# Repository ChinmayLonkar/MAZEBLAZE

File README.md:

# MAZEBLAZE

This repository contains hardware design files for the MAZEBLAZE Bot.This project is in developement and is not ready for final release.

It uses -
* TRCT5000 IR Sensors for following the lines on the maze 
* TB6612FNG Motor Driver for controlling two N20 motors
* ESP32 for control and perform tasks at high speeds and accuracy

Following are some images of the PCB Design

* Top View

* Bottom View

* Front Copper Layer

* Bottom Copper Layer

* Routing

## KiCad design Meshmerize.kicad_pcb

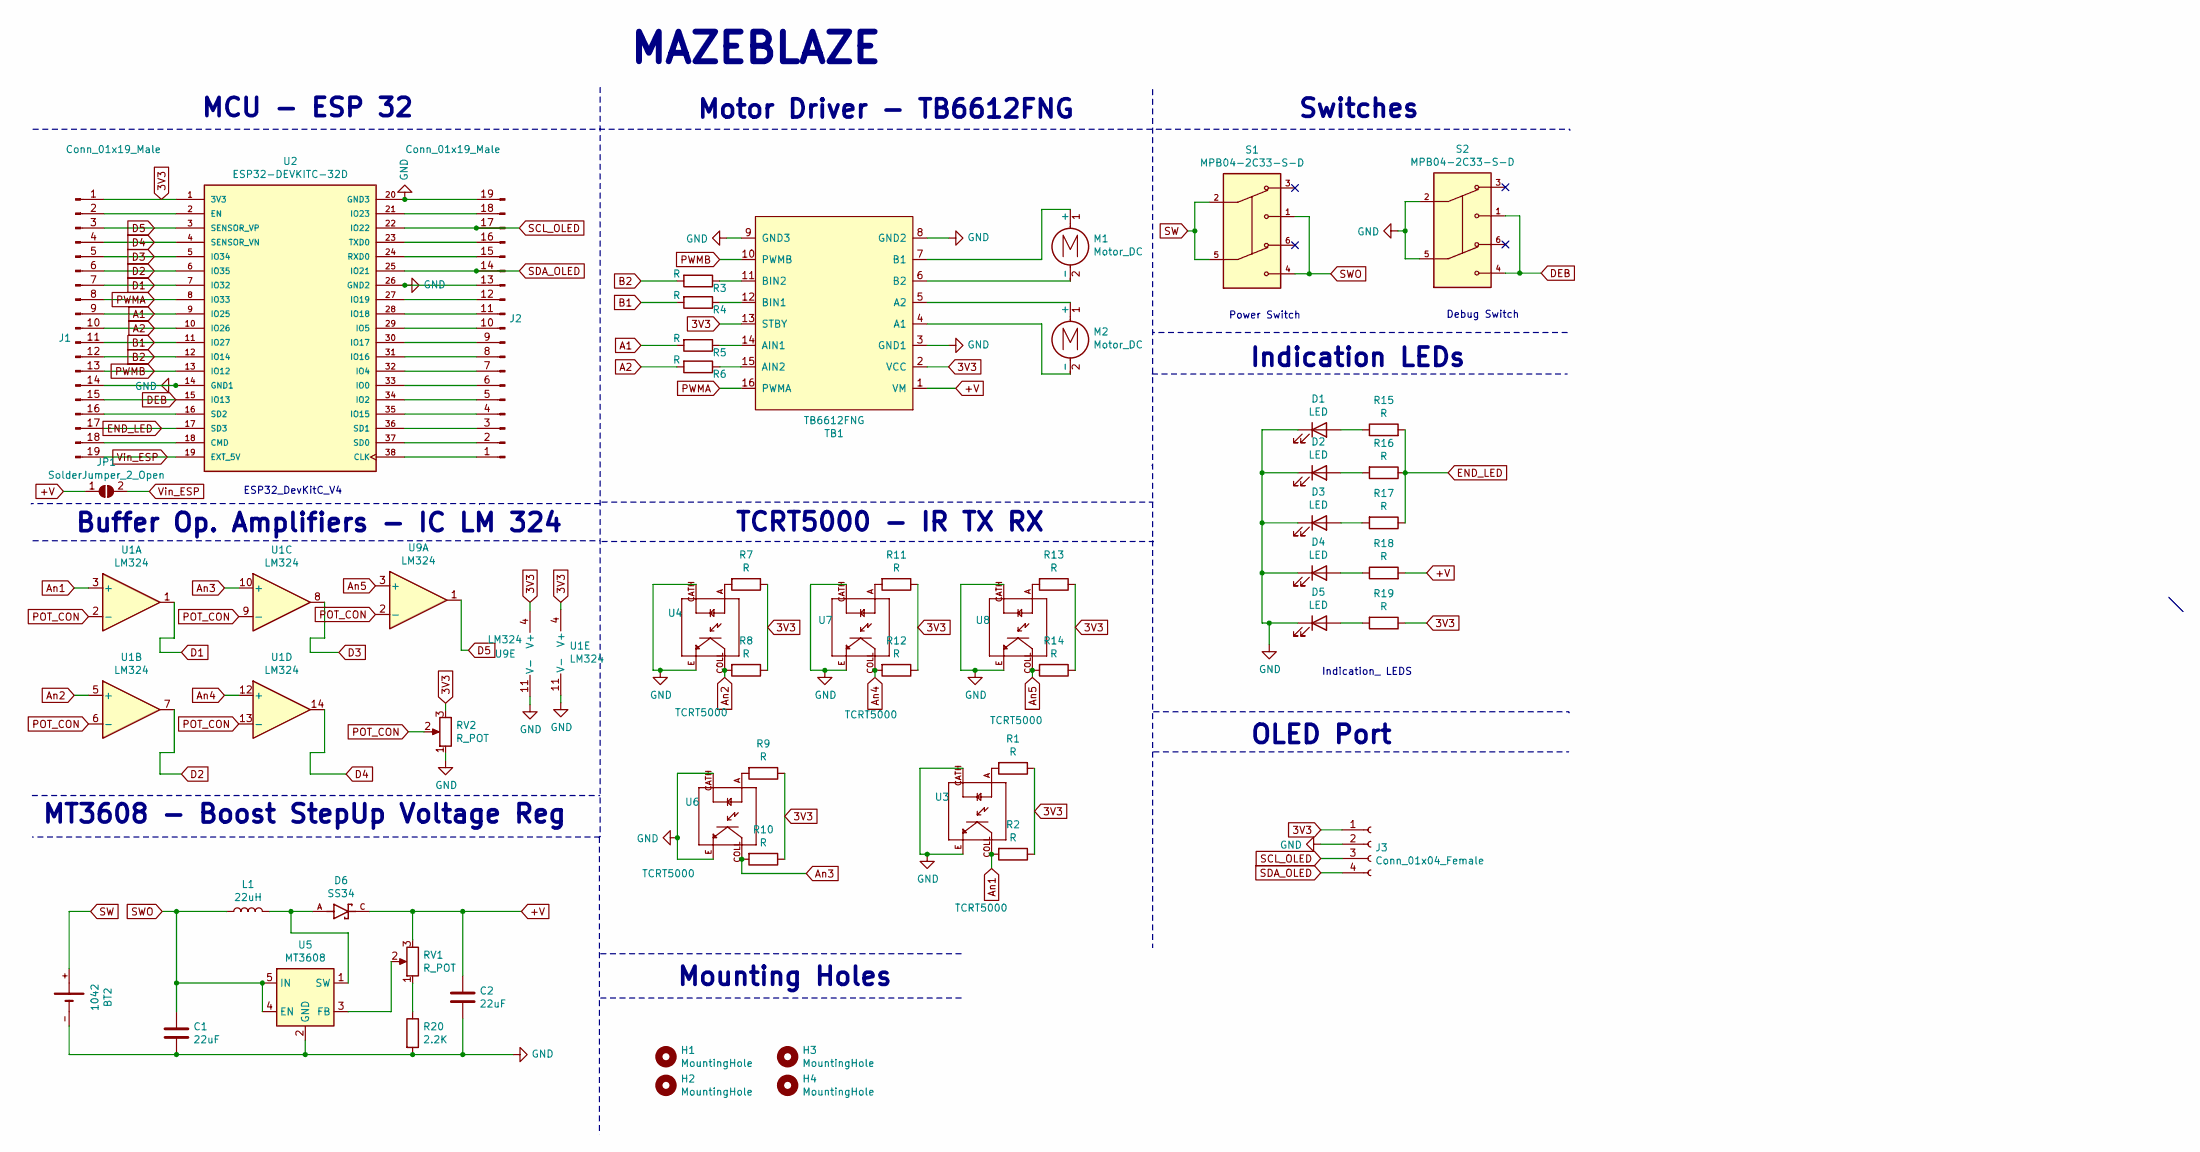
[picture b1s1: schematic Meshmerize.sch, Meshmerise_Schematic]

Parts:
BT2: 1042; BAT_1042
C1, C2: 22uF; C_0805_2012Metric
D1, D2, D3, D4, D5: LED; LED_1206_3216Metric
D6: SS34; DIOM7959X265N; PARTREV 31 Aug 2016
H1, H2, H3, H4: MountingHole; MountingHole_2.2mm_M2
J1, J2: Conn_01x19_Male; PinHeader_1x19_P2.54mm_Vertical
J3: Conn_01x04_Female; PinSocket_1x04_P2.54mm_Vertical
JP1: SolderJumper_2_Open; SolderJumper-2_P1.3mm_Open_Pad1.0x1.5mm
L1: 22uH; L_12x12mm_H6mm
M1, M2: Motor_DC; N20_Motor
R1, R2, R3, R4, R5, R6, R7, R8, R9, R10, R11, R12, R13, R14, R15, R16, R17, R18, R19: R; R_1206_3216Metric
R20: 2.2K; R_1206_3216Metric
RV1, RV2: R_POT; TRIM_3296W-1-202LF
S1, S2: MPB04-2C33-S-D; SW_MPB04-2C33-S-D; PARTREV 1.0
TB1: TB6612FNG
U1, U9: LM324; SOIC-14_3.9x8.7mm_P1.27mm
U2: ESP32-DEVKITC-32D; MODULE_ESP32-DEVKITC-32D; PARTREV 4
U3, U4, U6, U7, U8: TCRT5000; OPTO_TCRT5000; PARTREV 1.7
U5: MT3608; SOT-23-6

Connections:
3V3: J1.1, J3.1, R1.1, R2.1, R7.1, R8.1, R9.1, R10.1, R11.1, R12.1, R13.1, R14.1, R19.1, RV2.3, TB1.2 (VCC), TB1.13 (STBY), U1.4 (V+), U2.1 (3V3), U9.4 (V+)
+V: C2.1, D6.C, JP1.1 (A), R18.2, RV1.3, TB1.1 (VM)
A1: J1.9, R5.2, U2.9 (IO25)
A2: J1.10, R6.2, U2.10 (IO26)
An1: R2.2, U1.3 (+), U3.COLL
An2: R8.2, U1.5 (+), U4.COLL
An3: R10.2, U1.10 (+), U6.COLL
An4: R12.2, U1.12 (+), U7.COLL
An5: R14.2, U8.COLL, U9.3 (+)
B1: J1.11, R4.2, U2.11 (IO27)
B2: J1.12, R3.2, U2.12 (IO14)
D1: J1.7, U1.1, U2.7 (IO32)
D2: J1.6, U1.7, U2.6 (IO35)
D3: J1.5, U1.8, U2.5 (IO34)
D4: J1.4, U1.14, U2.4 (SENSOR_VN)
D5: J1.3, U2.3 (SENSOR_VP), U9.1
DEB: J1.15, S2.1, S2.4, U2.15 (IO13)
END_LED: J1.17, R15.2, R16.1, R17.1, U2.17 (SD3)
GND: BT2.-, C1.2, C2.2, D1.1 (K), D2.1 (K), D3.1 (K), D4.1 (K), D5.1 (K), J1.14, J2.13, J2.19, J3.2, R20.2, RV2.1, S2.2, S2.5, TB1.3 (GND1), TB1.8 (GND2), TB1.9 (GND3), U1.11 (V-), U2.14 (GND1), U2.20 (GND3), U2.26 (GND2), U3.CATH, U3.E, U4.CATH, U4.E, U5.2 (GND), U6.CATH, U6.E, U7.CATH, U7.E, U8.CATH, U8.E, U9.11 (V-)
unnamed: D1.2 (A), R15.1
unnamed: D2.2 (A), R16.2
unnamed: D3.2 (A), R17.2
unnamed: D4.2 (A), R18.1
unnamed: D5.2 (A), R19.2
unnamed: D6.A, L1.2, U5.1 (SW)
unnamed: J1.2, U2.2 (EN)
unnamed: J1.16, U2.16 (SD2)
unnamed: J1.18, U2.18 (CMD)
unnamed: J2.1, U2.38 (CLK)
unnamed: J2.2, U2.37 (SD0)
unnamed: J2.3, U2.36 (SD1)
unnamed: J2.4, U2.35 (IO15)
unnamed: J2.5, U2.34 (IO2)
unnamed: J2.6, U2.33 (IO0)
unnamed: J2.7, U2.32 (IO4)
unnamed: J2.8, U2.31 (IO16)
unnamed: J2.9, U2.30 (IO17)
unnamed: J2.10, U2.29 (IO5)
unnamed: J2.11, U2.28 (IO18)
unnamed: J2.12, U2.27 (IO19)
unnamed: J2.15, U2.24 (RXD0)
unnamed: J2.16, U2.23 (TXD0)
unnamed: J2.18, U2.21 (IO23)
unnamed: M1.1 (+), TB1.7 (B1)
unnamed: M1.2 (-), TB1.6 (B2)
unnamed: M2.1 (+), TB1.5 (A2)
unnamed: M2.2 (-), TB1.4 (A1)
unnamed: R1.2, U3.A
unnamed: R3.1, TB1.11 (BIN2)
unnamed: R4.1, TB1.12 (BIN1)
unnamed: R5.1, TB1.14 (AIN1)
unnamed: R6.1, TB1.15 (AIN2)
unnamed: R7.2, U4.A
unnamed: R9.2, U6.A
unnamed: R11.2, U7.A
unnamed: R13.2, U8.A
unnamed: R20.1, RV1.1
unnamed: RV1.2, U5.3 (FB)
POT_CON: RV2.2, U1.2 (-), U1.6 (-), U1.9 (-), U1.13 (-), U9.2 (-)
PWMA: J1.8, TB1.16 (PWMA), U2.8 (IO33)
PWMB: J1.13, TB1.10 (PWMB), U2.13 (IO12)
SCL_OLED: J2.17, J3.3, U2.22 (IO22)
SDA_OLED: J2.14, J3.4, U2.25 (IO21)
SW: BT2.+, S1.2, S1.5
SWO: C1.1, L1.1, S1.1, S1.4, U5.4 (EN), U5.5 (IN)
Vin_ESP: J1.19, JP1.2 (B), U2.19 (EXT_5V)

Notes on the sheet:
Indication_ LEDS
ESP32_DevKitC_V4
MAZEBLAZE
MCU - ESP 32
Motor Driver - TB6612FNG
Switches
Debug Switch
Power Switch
Buffer Op. Amplifiers - IC LM 324
TCRT5000 - IR TX RX
MT3608 - Boost StepUp Voltage Reg
Mounting Holes
Indication LEDs
OLED Port

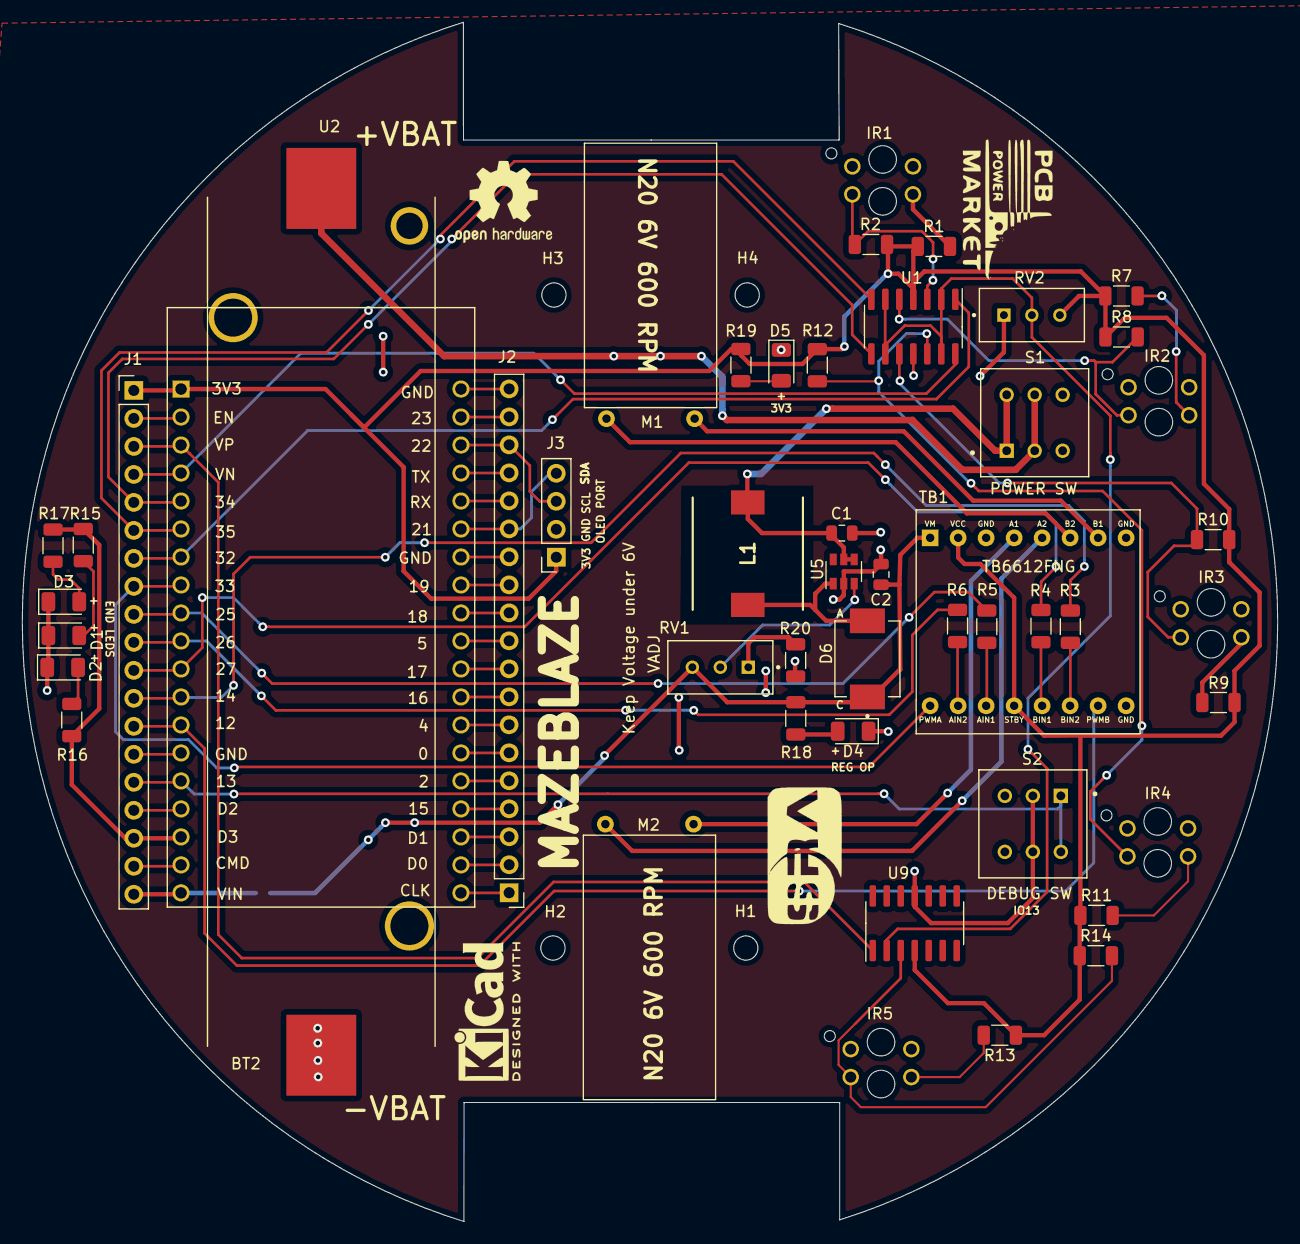
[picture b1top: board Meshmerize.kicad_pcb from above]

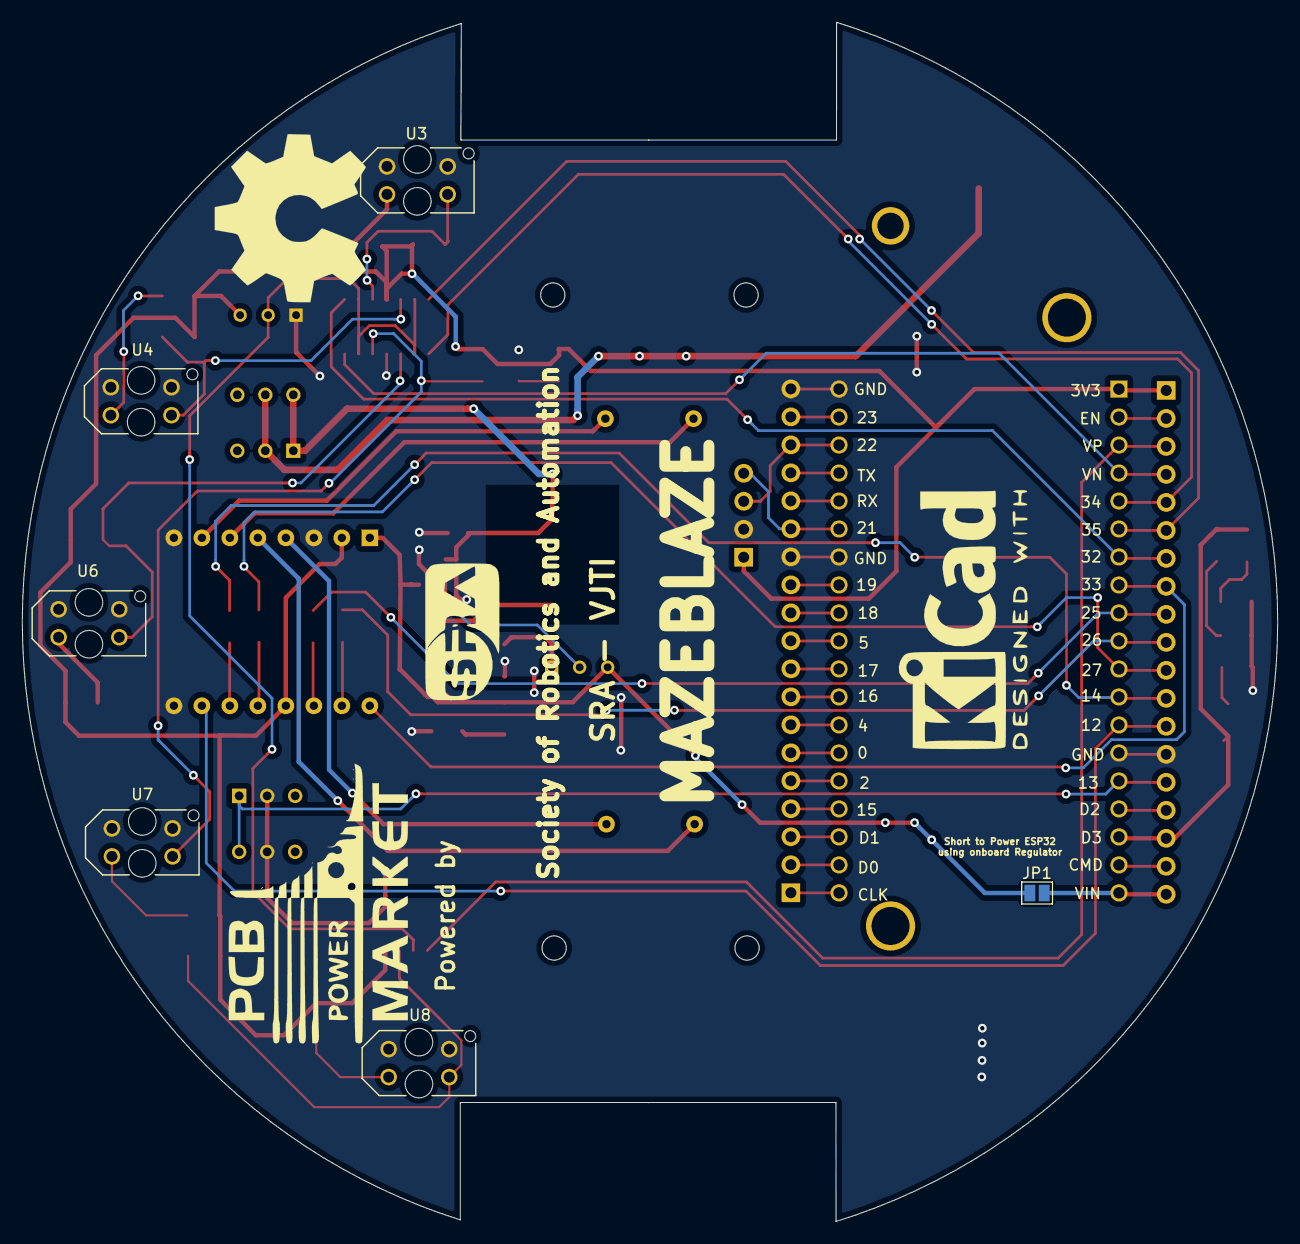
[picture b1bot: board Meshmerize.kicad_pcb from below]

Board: 2 copper layers, 113.9 x 108.8 mm, 54 parts (6 on the bottom side), 66 nets.

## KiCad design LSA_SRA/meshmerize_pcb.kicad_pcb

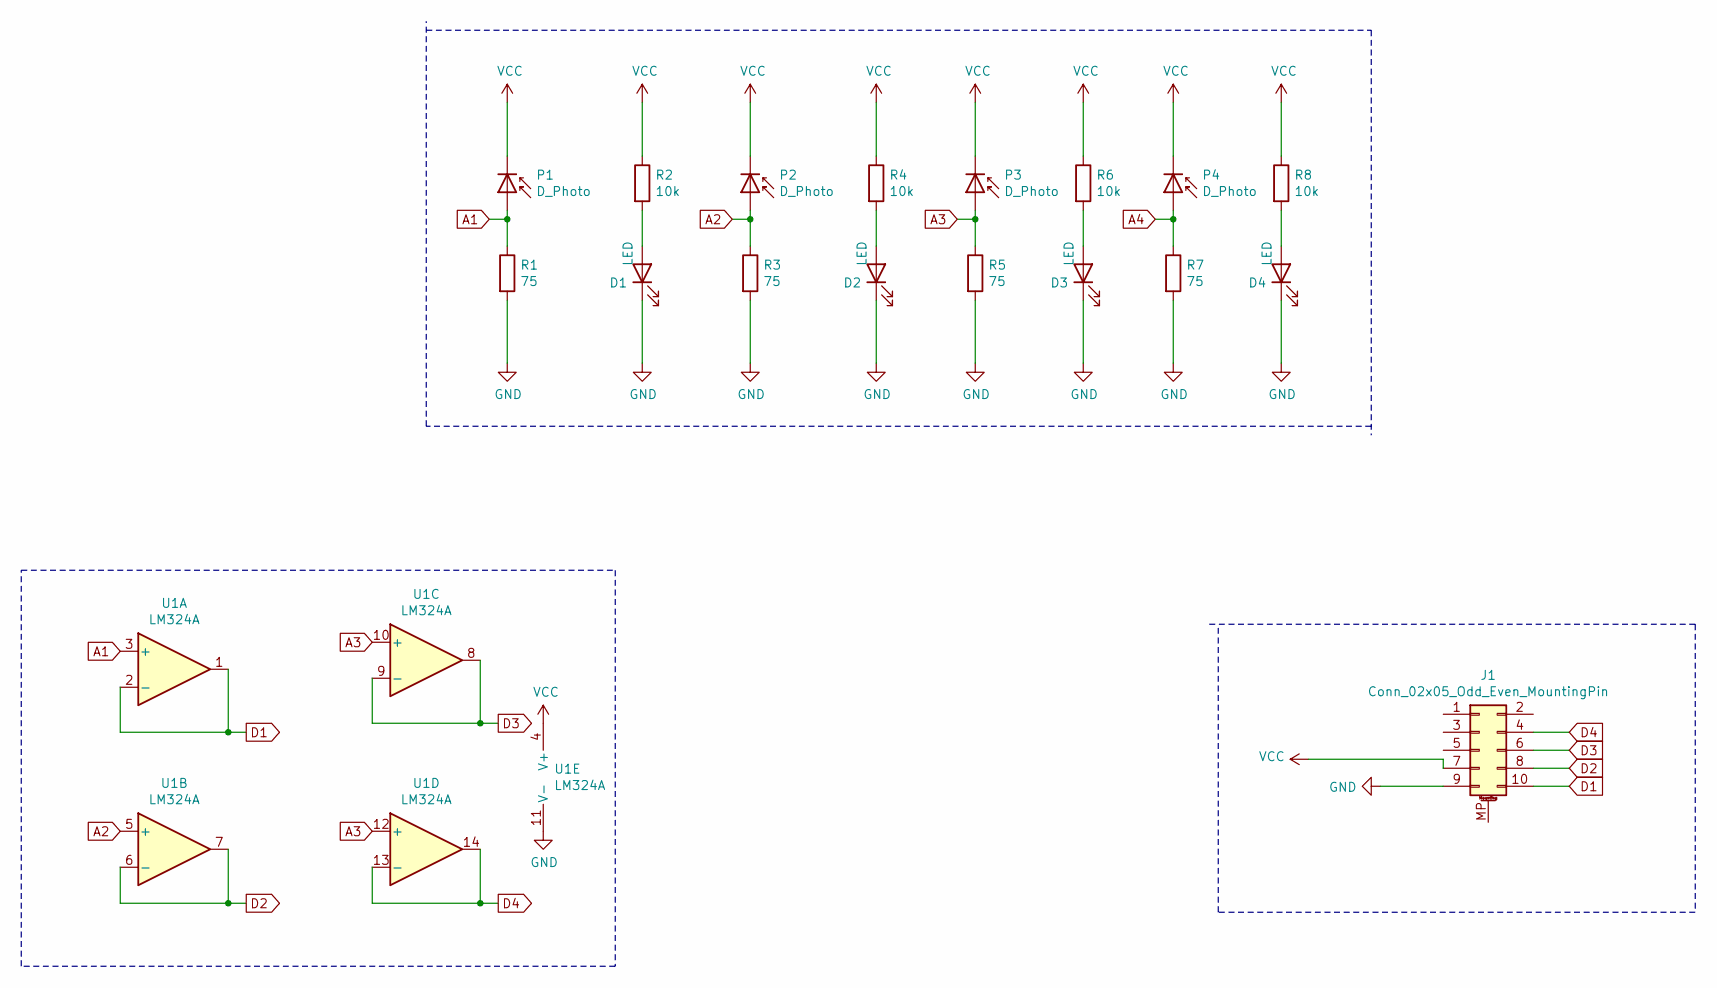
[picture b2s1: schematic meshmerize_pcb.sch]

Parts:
D1, D2, D3, D4: LED; LED_D3.0mm
J1: Conn_02x05_Odd_Even_MountingPin; IDC-Header_2x05-1MP_P2.54mm_Latch6.5mm_Vertical
P1, P2, P3, P4: D_Photo; LED_D5.0mm
R1, R3, R5, R7: 75; R_Axial_DIN0207_L6.3mm_D2.5mm_P10.16mm_Horizontal
R2, R4, R6, R8: 10k; R_Axial_DIN0207_L6.3mm_D2.5mm_P10.16mm_Horizontal
U1: LM324A; LM324-PDIP

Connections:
A1: P1.2 (A), R1.1, U1.3 (+)
A2: P2.2 (A), R3.1, U1.5 (+)
A3: P3.2 (A), R5.1, U1.10 (+), U1.12 (+)
A4: P4.2 (A), R7.1
D1: J1.10, U1.1, U1.2 (-)
D2: J1.8, U1.6 (-), U1.7
D3: J1.6, U1.8, U1.9 (-)
D4: J1.4, U1.13 (-), U1.14
GND: D1.1 (K), D2.1 (K), D3.1 (K), D4.1 (K), J1.9, R1.2, R3.2, R5.2, R7.2, U1.11 (V-)
unnamed: D1.2 (A), R2.2
unnamed: D2.2 (A), R4.2
unnamed: D3.2 (A), R6.2
unnamed: D4.2 (A), R8.2
VCC: J1.7, P1.1 (K), P2.1 (K), P3.1 (K), P4.1 (K), R2.1, R4.1, R6.1, R8.1, U1.4 (V+)

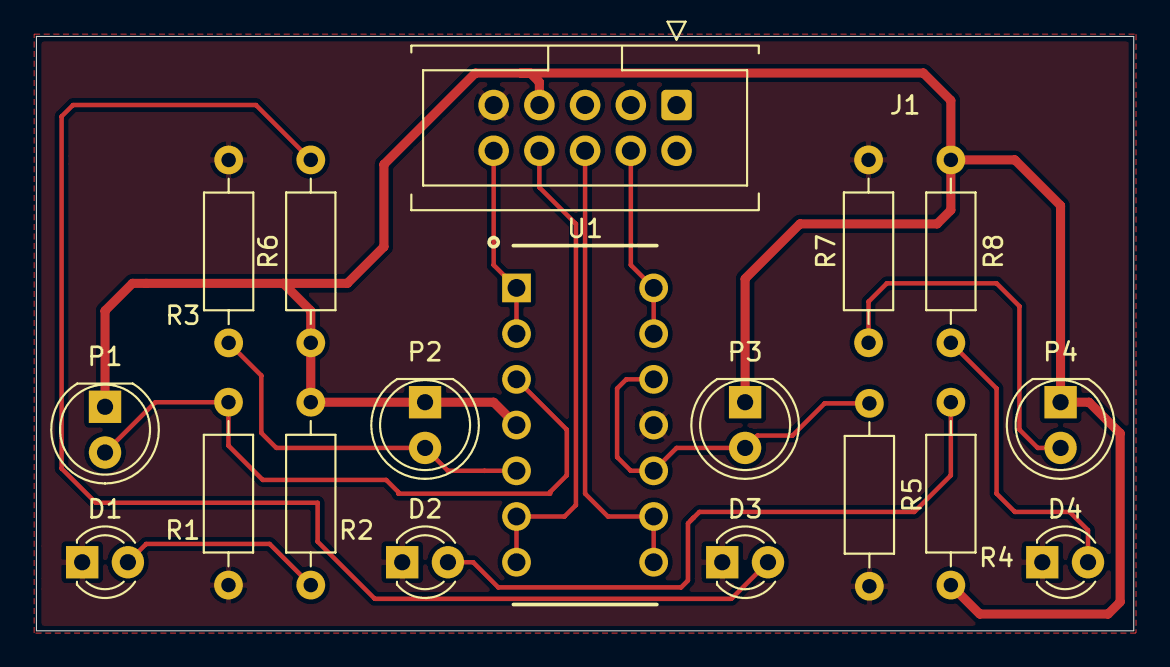
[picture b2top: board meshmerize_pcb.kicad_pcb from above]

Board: 2 copper layers, 61.0 x 33.0 mm, 18 parts (0 on the bottom side), 14 nets.

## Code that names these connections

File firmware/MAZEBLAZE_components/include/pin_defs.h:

#ifndef PIN_DEFS_H
#define PIN_DEFS_H

#define CHECK(x)                \
    do                          \
    {                           \
        esp_err_t __;           \
        if ((__ = x) != ESP_OK) \
            return __;          \
    } while (0)
#define CHECK_LOGE(err, x, tag, msg, ...)      \
    do                                         \
    {                                          \
        if ((err = x) != ESP_OK)               \
        {                                      \
            ESP_LOGE(tag, msg, ##__VA_ARGS__); \
            return err;                        \
        }                                      \
    } while (0)



#define END_LED 10

#define DEBUG_SWITCH 13


#define LSA_D0 32
#define LSA_D1 35
#define LSA_D2 34
#define LSA_D3 39
#define LSA_D4 36

#define SCL_OLED 22
#define SDA_OLED 21

/////// motor driver ////////
//****** normal mode ******//
#define PWM_A 33 //MCPWM_UNIT_1 MCPWM0A
#define AIN_1 25 //MCPWM_UNIT_1 MCPWM0B
#define AIN_2 26 //MCPWM_UNIT_1 MCPWM1A
#define PWM_B 12 //MCPWM_UNIT_1 MCPWM1B
#define BIN_1 27 //MCPWM_UNIT_1 MCPWM2A
#define BIN_2 14 //MCPWM_UNIT_1 MCPWM2B

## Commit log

2021-11-16 Added .gitignore
2021-11-16 Added Kicad project for Meshmerize bot
2021-11-17 Completed PCB Routing
2021-11-17 Changes made in footprint
2021-11-17 Optimized schematics, routing and performed clean up
2021-11-17 Added R-Pot for LSA sensitivity, jumper to power ESP32 using inbuilt regulator, minor optimizations
2021-11-17 Modified Silkscreen and created Gerber Files
2021-11-17 Made minor changes in Back silkscreen and front copper traces
2021-11-17 Stitched Vias for Continuous Ground Plane, minor silkscreen fixes
2021-11-18 Added 3D Files
2021-11-18 Added Logos
2021-11-18 Added silkscreen, asset images, updated renders and gerbers
2021-11-19 Fixed errors, optlized routing
2021-11-19 Updated readme file and gerbers
2021-11-19 Shortened MAZEBLAZE title on B.silk
2021-11-19 Updated Gerbers after minor silkscreen fixes
2021-11-19 Updated Assets with latest render images
2021-11-20 Added firmware
2021-11-23 PCB design files for MAZEBLAZE bot
2021-11-23 Updated firmware with some minor fixes
2021-11-23 Added Motor Component
2021-11-23 Added a basic example for running motor
2021-11-25 Added 4_line_following
2021-11-25 Removed build files
2021-11-26 Added wifi_component
2021-11-26 Implement Wifi for changing PID values
2021-11-27 Setup for White and Black margins
2021-11-27 LSA + Motor control
2021-11-27 made a new function in line_following.c
2021-11-29 Changes made in motor configration as per hardware setup
2021-11-29 Made changes in motor driver component according to hardware setup
2021-11-30 Rearranges file format
2021-11-30 Adds line_following in examples
2021-11-30 Restructures previous code in modular format
2021-12-01 Adds ESP WIFI LOGGER component
2021-12-01 Creates the mazeblaze board component
2021-12-01 Corrects the linefollwing bug
2021-12-01 Adds sdkconfig to gitignore
2021-12-01 Refactores and solves minor error
2021-12-01 Enables WiFi connection
2021-12-01 Code flow optimized
2021-12-02 Updated Cmake list
2021-12-02 Removed Wifi function
2021-12-02 CMake list changed
2021-12-02 Modified motor Algorithm
2021-12-02 Corrects the menu name in kconfig
2021-12-03 Removes Redundant Wifi Handler files
    With Inclusion of Wifi logger the example connect is uesd for connecting
    with the wifi and hence the wifi_handler.h and wifi_handler.c are being
    removed
2021-12-03 Adds Wifi logger component supports
    The wifi logger makes it easy to debug using the wifi. The existing
    ESP_LOGX logs can be routed directly . The default communication
    protocol used will be UDP (recommeneded) while there is option for TCP
    as well.
2022-01-16 Added to new branch
2022-02-08 PID and turn issues resolved
2022-02-08 resolved LSA component issues
2022-02-08 PWM pin issue resolved
2022-02-17 New firmware
2022-02-17 Firmware update
2022-02-17 left follow complete
2022-02-18 turn store feature
2022-02-19 Merged loops
2022-02-19 led initial OFF state
2022-02-19 fixed minor errors
2022-10-08 add tweaks
2022-10-08 more tweaks
